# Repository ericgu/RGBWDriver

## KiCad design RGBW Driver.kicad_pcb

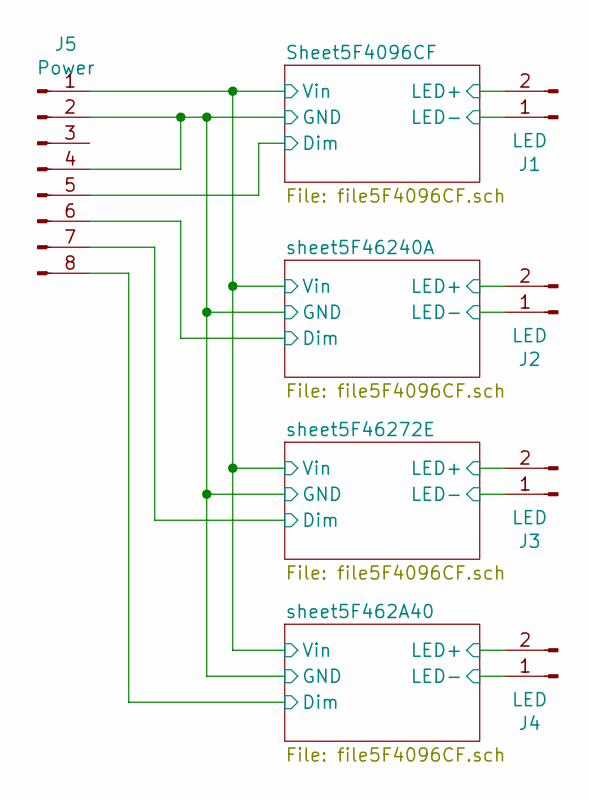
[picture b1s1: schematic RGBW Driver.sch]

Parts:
J1, J2, J3, J4: LED; Pin_Header_Straight_1x02_Pitch2.54mm
J5: Power; Pin_Header_Straight_1x08_Pitch2.54mm

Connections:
/Dim1: J5.5; also elsewhere on the board
/Dim2: J5.6; also elsewhere on the board
/Dim3: J5.7; also elsewhere on the board
/Dim4: J5.8; also elsewhere on the board
/Gnd: J5.2, J5.4; also elsewhere on the board
/LED1+: J1.2; also elsewhere on the board
/LED1-: J1.1; also elsewhere on the board
/LED2+: J2.2; also elsewhere on the board
/LED2-: J2.1; also elsewhere on the board
/LED3+: J3.2; also elsewhere on the board
/LED3-: J3.1; also elsewhere on the board
/LED4+: J4.2; also elsewhere on the board
/LED4-: J4.1; also elsewhere on the board
/Vin: J5.1; also elsewhere on the board

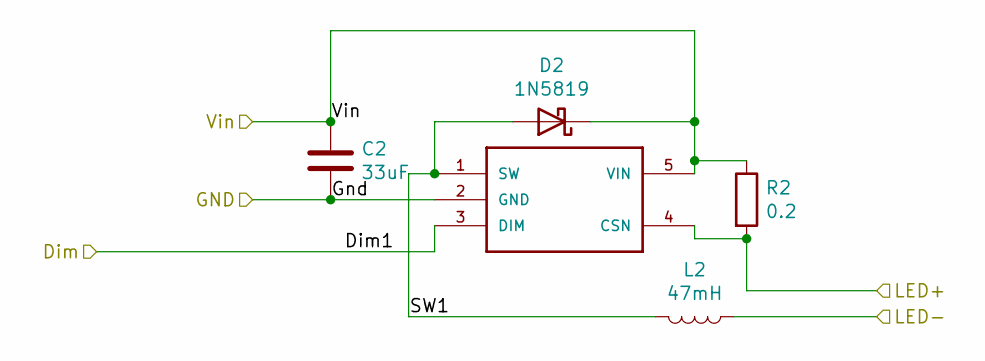
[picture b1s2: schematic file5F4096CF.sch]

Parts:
C1: 33uF; C_1210; LCSC C308920
D1: 1N5819; D_SOD-123; LCSC C369930
L1: 47mH; L_12x12mm_h6mm; LCSC C169398
R1: 0.2; R_1206; LCSC C25335
U1: PT4115; SOT-89-5_Housing; LCSC C15425

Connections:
/Dim1: U1.3 (DIM); also elsewhere on the board
/Gnd: C1.2, U1.2 (GND); also elsewhere on the board
/LED1+: R1.2, U1.4 (CSN); also elsewhere on the board
/LED1-: L1.1; also elsewhere on the board
/SW1: D1.2 (A), L1.2, U1.1 (SW)
/Vin: C1.1, D1.1 (K), R1.1, U1.5 (VIN); also elsewhere on the board

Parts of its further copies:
C2, C3, C4: 33uF; C_1210; LCSC C308920
D2, D3, D4: 1N5819; D_SOD-123; LCSC C369930
L2, L3, L4: 47mH; L_12x12mm_h6mm; LCSC C169398
R2, R3, R4: 0.2; R_1206; LCSC C25335
U2, U3, U4: PT4115; SOT-89-5_Housing; LCSC C15425

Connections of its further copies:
/Dim2: U2.3 (DIM); also elsewhere on the board
/Dim3: U3.3 (DIM); also elsewhere on the board
/Dim4: U4.3 (DIM); also elsewhere on the board
/Gnd: C2.2, C3.2, C4.2, U2.2 (GND), U3.2 (GND), U4.2 (GND); also elsewhere on the board
/LED2+: R2.2, U2.4 (CSN); also elsewhere on the board
/LED2-: L2.1; also elsewhere on the board
/LED3+: R3.2, U3.4 (CSN); also elsewhere on the board
/LED3-: L3.1; also elsewhere on the board
/LED4+: R4.2, U4.4 (CSN); also elsewhere on the board
/LED4-: L4.1; also elsewhere on the board
/SW2: D2.2 (A), L2.2, U2.1 (SW)
/SW3: D3.2 (A), L3.2, U3.1 (SW)
/SW4: D4.2 (A), L4.2, U4.1 (SW)
/Vin: C2.1, C3.1, C4.1, D2.1 (K), D3.1 (K), D4.1 (K), R2.1, R3.1, R4.1, U2.5 (VIN), U3.5 (VIN), U4.5 (VIN); also elsewhere on the board

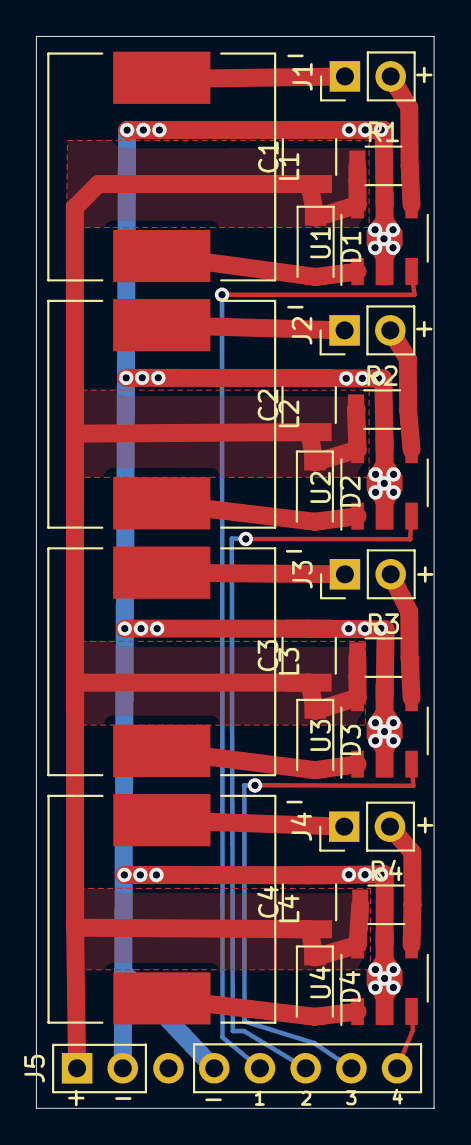
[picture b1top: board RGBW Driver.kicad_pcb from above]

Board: 2 copper layers, 22.1 x 59.5 mm, 25 parts (0 on the bottom side), 18 nets.

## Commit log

2020-08-20 first version
2020-08-20 Place-replicate the layout
    also replaced some trackign with filled zones.
2020-08-22 single and double versions
2020-08-24 two driver version
